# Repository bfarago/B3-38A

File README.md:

# B3-38A
B3-38A or V3-38A Russian Millivoltmeter

REVERSE ENGINEERING
-------------------
This repository contains all the collected informations regarding the old russian millivoltmeter instrument. The goal to collect datasheets, schematics, etc.

[BOM](rv_doc/bom.md), [Service Manual](rv_doc/B3-38A.pdf)

Technical characteristics
-------------------------
Millivoltmeter V3-38A (V3 38A, V338A, b3-38a, b338a, b3 38a)

Designed to measure the rms AC voltage sine wave of 0.1 mV to 300 V in the frequency range from 20 Hz to 5 MHz.
The span value of 1 mV, 3mV, 10mV, 30mV, 100mV, 300mV, 1V, 3V, 10V, 30V, 100V and 300V
The basic error of ± 2,5%

Millivoltmeter V3-38A is designed to measure the rms AC voltage sine wave of 0.1 mV to 300 V in the frequency range from 20 Hz to 5 MHz.
The operating conditions of use of the instrument Millivoltmeter V3-38A: ambient temperature from 10 ° to 35 ° C;
relative humidity. air 80% at 25 ° C, atmospheric pressure from 86 to 106 kPa (650 to 800 mm Hg. st.) mains (220 ± 22), frequency (50 ± 0,5) Hz .
Technical Data is a
Measurement range of the instrument voltages from 300V to 100mkV overlapping ranges with upper limits of 1 mV, 3mV, 10mV, 30mV, 100mV, 300mV, 1V, 3V, 10V, 30V, 100V and 300V. Instrument measures the voltage in the frequency range from 20 Hz to 5 MHz .
The range of frequencies of the device Millivoltmeter V3-38A has a working range of frequencies:
I from 45 Hz to 1 MHz (on);
II from 20 to 45 Hz (except);
III St.. 1 to 3 MHz (on);
IV St.. 3 to 5 MHz (inclusive).
Frequency of calibration of 1 kHz. Primary instrument error, expressed as a percentage of the upper limit established by sub-band measurements, no more than ± 2,5%.
Instrument error Millivoltmeter V3-38A in the working frequency regions, expressed as a percentage of the upper limit of the established sub-band, and the change of readings within the operating frequency ranges with respect to the frequency of calibration readings in percent, do not exceed the values shown in Table. 1.

Table 1: The limits of permissible errors (beyond the assumed changes of reading),%

| Subranges | I.: 45Hz- 1 MHz | II.: 20 - 45 Hz | III.:  1 - 3 MHz | IV.: 3 - 5 MHz |
| --- | --- | --- | --- | --- |
| 1 mV-300mV | ± 2,5 % | ± 4,0 (± 4,0) % | ± 4,0 (± 4,0) % | ± 6,0 (± 6,0) % |
| 1V-300V | ± 2,5 % | ± 4,0 (± 4,0) % | ± 6,0 (± 6,0) % | ± 6,0 (± 6,0) % |

Change readings, caused by changes in temperature. Ambient air from the normal to any temperature within the operating temperature range does not exceed the basic error for every 10 ° C change in temperature.
Change readings Millivoltmeter V3-38A, expressed as a percentage of the upper limit established by sub-band, rejecting the shape of the measured voltage from the sinusoidal (THD less than 20%) is less than half the value of the harmonic content in percent.
The deviation of the index from scratch, due to the intrinsic noise does not exceed 5% of the upper limit established by sub-band measurements with closed-circuit input.
The device retains its specifications within the rules, if its input DC voltage is not more than 250-V
Response time the device is less than 4 seconds.
Millivoltmeter V3-38A save tons of basic error handling five times after exposure to stress, but not more than 600 V.
Active impedance device, measured at a frequency of 45 Hz, less than 5 megohms at subbands upper limits 1-300mV and at least 4 Mohms subbands upper limits in 1-300
Input capacitance unit is not more than 25 pF subbands upper limits of 1-300 mV and not more than 15 pF subbands upper limits of 1-300 W.
The capacity of each of the connecting cable is not more than 80 pF. Warm-up time 15 min. Millivoltmeter V3-38A retains its specifications when powered from the mains AC voltage (220 ± 22) V (50 ± 0,5) Hz.
The power consumed by the network at a nominal voltage not exceeding 6 VA. Device allows continuous operation in the working conditions for 8 hours

Unit weight Millivoltmeter V3-38A or less than 3.2 kg.

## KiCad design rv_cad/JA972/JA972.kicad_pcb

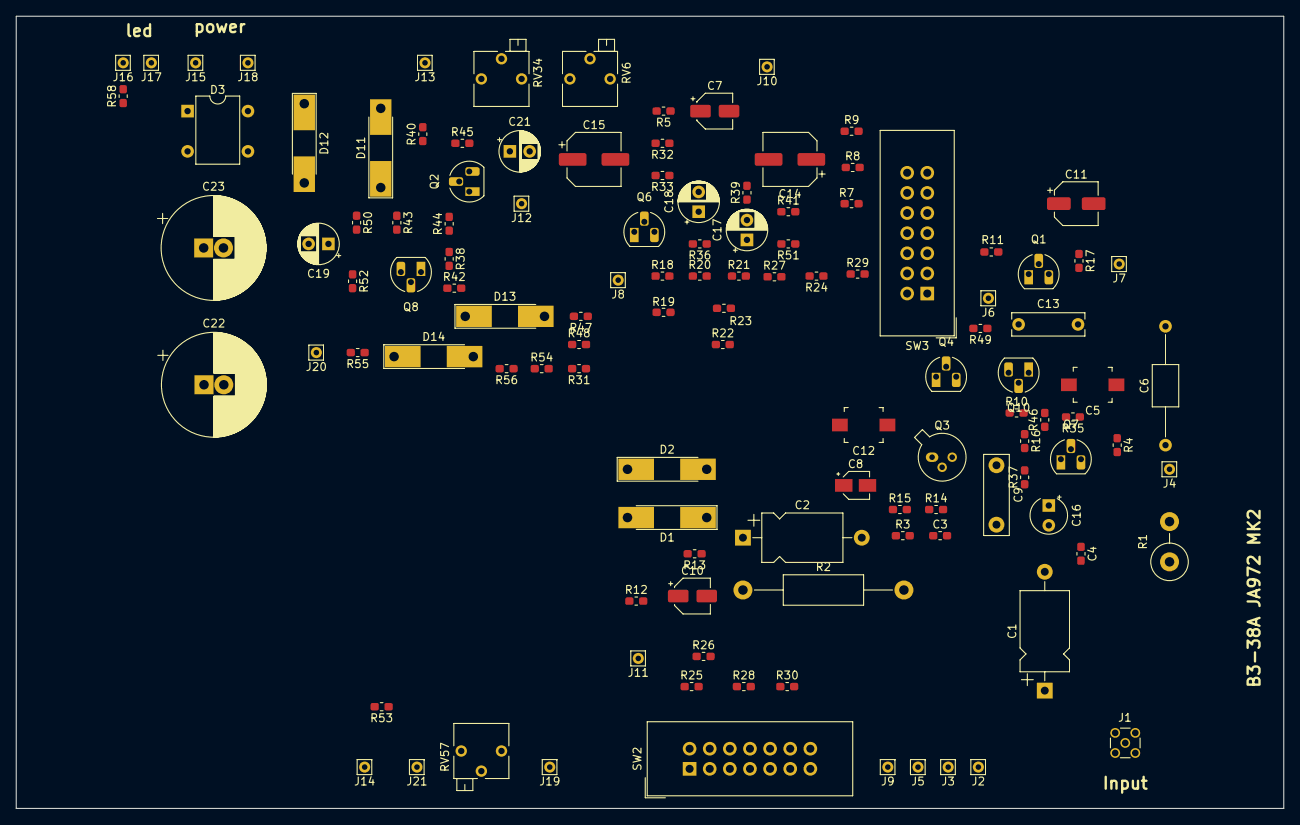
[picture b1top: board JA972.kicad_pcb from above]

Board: 2 copper layers, 160.0 x 100.0 mm, 118 parts (0 on the bottom side), 61 nets, no tracks yet.

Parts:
C1: 1600 500V 5%; CP_Axial_L10.0mm_D6.0mm_P15.00mm_Horizontal
C2: 2700 500V 5%; CP_Axial_L10.0mm_D6.0mm_P15.00mm_Horizontal
C3: 150 10%; C_0603_1608Metric_Pad1.05x0.95mm_HandSolder
C4: 2p2; C_0603_1608Metric_Pad1.05x0.95mm_HandSolder
C5: 2/7; C_Trimmer_Murata_TZB4-B
C6: 0,047uF/400V/10%; C_Axial_L5.1mm_D3.1mm_P15.00mm_Horizontal
C7: 200u/25V; CP_Elec_4x5.4
C8: 1u/6v3; CP_Elec_3x5.3
C9: 15+-10%/ M47; C_Rect_L10.0mm_W3.0mm_P7.50mm_FKS3_FKP3
C10: 22u/20v; CP_Elec_4x5.8
C11: 200u/25v; CP_Elec_5x5.8
C12: CTRIM; C_Trimmer_Murata_TZB4-B
C13: 15+-10%/ M47; C_Rect_L9.0mm_W2.7mm_P7.50mm_MKT
C14: 200u/25v; CP_Elec_6.3x5.4_Nichicon
C15: 100u/6v3; CP_Elec_6.3x5.4_Nichicon
C16: x; CP_Radial_Tantal_D4.5mm_P2.50mm
C17, C18, C19: x; CP_Radial_D5.0mm_P2.50mm
C21: 200u/25v; CP_Radial_D5.0mm_P2.50mm
C22: 100u/50v; CP_Radial_D13.0mm_P2.50mm
C23: 50u/100v; CP_Radial_D13.0mm_P2.50mm
D1, D2, D13, D14: KD522B; D_MELF-RM10_Universal_Handsoldering
D3: D_Bridge_+-AA; Diode_Bridge_DIP-4_W7.62mm_P5.08mm
D11, D12: 12V; D_MELF-RM10_Universal_Handsoldering
J1: Conn_Coaxial; MMCX_Molex_73415-1471_Vertical
J2: PGM_SWITCH1; Pin_D0.7mm_L6.5mm_W1.8mm_FlatFork
J3, J5: PGM_SWITCH2; Pin_D0.7mm_L6.5mm_W1.8mm_FlatFork
J4: PGM_SWITCH3; Pin_D0.7mm_L6.5mm_W1.8mm_FlatFork
J6: E1; Pin_D0.7mm_L6.5mm_W1.8mm_FlatFork
J7, J8: P7; Pin_D0.7mm_L6.5mm_W1.8mm_FlatFork
J9, J10: P10; Pin_D0.7mm_L6.5mm_W1.8mm_FlatFork
J11: P11; Pin_D0.7mm_L6.5mm_W1.8mm_FlatFork
J12: E2; Pin_D0.7mm_L6.5mm_W1.8mm_FlatFork
J13: E3; Pin_D0.7mm_L6.5mm_W1.8mm_FlatFork
J14: P6; Pin_D0.7mm_L6.5mm_W1.8mm_FlatFork
J15: P2; Pin_D0.7mm_L6.5mm_W1.8mm_FlatFork
J16: P4; Pin_D0.7mm_L6.5mm_W1.8mm_FlatFork
J17: P1; Pin_D0.7mm_L6.5mm_W1.8mm_FlatFork
J18: P3; Pin_D0.7mm_L6.5mm_W1.8mm_FlatFork
J19, J20, J21: P5; Pin_D0.7mm_L6.5mm_W1.8mm_FlatFork
Q1, Q2, Q4, Q6, Q7, Q8, Q10: 3107B; TO-92_HandSolder
Q3: kp103l; TO-18-3
R1: 7k5; R_Axial_DIN0414_L11.9mm_D4.5mm_P5.08mm_Vertical
R2: 5k11; R_Axial_DIN0411_L9.9mm_D3.6mm_P20.32mm_Horizontal
R3: 21,8; R_0603_1608Metric_Pad1.05x0.95mm_HandSolder
R4: 5M11; R_0603_1608Metric_Pad1.05x0.95mm_HandSolder
R5: 47k; R_0603_1608Metric_Pad1.05x0.95mm_HandSolder
R7, R44: 510; R_0603_1608Metric_Pad1.05x0.95mm_HandSolder
R8: 2M7; R_0603_1608Metric_Pad1.05x0.95mm_HandSolder
R9: 220k; R_0603_1608Metric_Pad1.05x0.95mm_HandSolder
R10, R35: 5k6; R_0603_1608Metric_Pad1.05x0.95mm_HandSolder
R11, R13: 3k; R_0603_1608Metric_Pad1.05x0.95mm_HandSolder
R12: 51; R_0603_1608Metric_Pad1.05x0.95mm_HandSolder
R14, R38, R39, R47, R50, R51: 1k; R_0603_1608Metric_Pad1.05x0.95mm_HandSolder
R15: 402; R_0603_1608Metric_Pad1.05x0.95mm_HandSolder
R16: 390; R_0603_1608Metric_Pad1.05x0.95mm_HandSolder
R17: 150; R_0603_1608Metric_Pad1.05x0.95mm_HandSolder
R18, R21, R24, R27: 56k; R_0603_1608Metric_Pad1.05x0.95mm_HandSolder
R19, R22, R25, R28, R30: 357; R_0603_1608Metric_Pad1.05x0.95mm_HandSolder
R20, R23, R26, R29, R52: 240; R_0603_1608Metric_Pad1.05x0.95mm_HandSolder
R31: 165; R_0603_1608Metric_Pad1.05x0.95mm_HandSolder
R32: 22k; R_0603_1608Metric_Pad1.05x0.95mm_HandSolder
R33, R37: 110; R_0603_1608Metric_Pad1.05x0.95mm_HandSolder
R36: 10; R_0603_1608Metric_Pad1.05x0.95mm_HandSolder
R40: 33k; R_0603_1608Metric_Pad1.05x0.95mm_HandSolder
R41: 100; R_0603_1608Metric_Pad1.05x0.95mm_HandSolder
R42, R45: 2k2; R_0603_1608Metric_Pad1.05x0.95mm_HandSolder
R43: 15; R_0603_1608Metric_Pad1.05x0.95mm_HandSolder
R46: 680; R_0603_1608Metric_Pad1.05x0.95mm_HandSolder
R48: 55,6; R_0603_1608Metric_Pad1.05x0.95mm_HandSolder
R49: 91; R_0603_1608Metric_Pad1.05x0.95mm_HandSolder
R53, R54: 1M; R_0603_1608Metric_Pad1.05x0.95mm_HandSolder
R55, R56: 2,49k; R_0603_1608Metric_Pad1.05x0.95mm_HandSolder
R58: 6k8; R_0603_1608Metric_Pad1.05x0.95mm_HandSolder
RV6: 33k; Potentiometer_Bourns_3266P_Horizontal
RV34: 220k; Potentiometer_Bourns_3266P_Horizontal
RV57: 1k5; Potentiometer_Bourns_3266P_Horizontal
SW2, SW3: SW_Rotary12; IDC-Header_2x07_P2.54mm_Vertical

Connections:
/P7: C11.2, C13.2, J7.1, J8.1, R17.1, R18.1, R19.1
/P8: C5.1, C6.1, J3.1, J5.1, R4.1
/PE2: J12.1, Q2.1, Q10.3, R16.2, R35.2, R37.2, R42.2, R46.1
GNDA: C1.1, C2.1, C7.2, C9.2, C10.2, C12.2, C15.1, C16.2, C19.2, C22.1, C23.1, D3.1, D12.2, J1.2, J11.1, J15.1, R2.1, R3.1, R13.1, R15.1, R20.2, R23.2, R26.2, R29.2, R31.2, R36.1, R38.1, R44.1, R45.1, R48.1, RV6.3, SW3.7, SW3.8, SW3.9, SW3.10, SW3.11, SW3.12
unnamed: C1.2, R1.1
unnamed: C2.2, C3.2, J4.1, R1.2, R2.2
unnamed: C3.1, R3.2
unnamed: C4.1, C5.2
unnamed: C4.2, J1.1, J2.1, R4.2
unnamed: C6.2, R7.2
unnamed: C7.1, Q1.1, R5.1, R10.2, R11.2, R16.1
unnamed: C8.1, D1.2, D2.1, R8.1, R9.2
unnamed: C9.1, Q3.3, Q4.2, R10.1
unnamed: C10.1, R12.1, R13.2
unnamed: C11.1, J6.1, Q1.3, R14.2
unnamed: C8.2, C12.1, Q3.1, R14.1, R15.2
unnamed: C13.1, R17.2, SW3.1, SW3.2
unnamed: C14.1, J10.1
unnamed: C14.2, R32.1, R33.1
unnamed: C15.2, R32.2, RV34.2, RV34.3
unnamed: C16.1, Q7.1, R37.1
unnamed: C17.1, C18.1, R41.2, R51.2
unnamed: C17.2, Q6.3, R36.2, R39.1, R41.1
unnamed: C18.2, R39.2
unnamed: C19.1, Q8.3, R43.2
unnamed: C21.1, D13.1, D14.2
unnamed: C21.2, J13.1, Q2.3, R45.2
unnamed: C22.2, R49.2, R50.2, R52.1
unnamed: C23.2, D3.2, R52.2, R58.1
unnamed: D1.1, D2.2, Q3.2, R7.1, R8.2
unnamed: D3.3, J17.1
unnamed: D3.4, J18.1
unnamed: D11.1, Q10.2, R50.1
unnamed: D11.2, D12.1
unnamed: D13.2, R47.2, R54.1, R56.1
unnamed: D14.1, R53.1, R55.1
unnamed: J9.1, SW2.13
unnamed: J14.1, R53.2
unnamed: J16.1, R58.2
unnamed: J19.1, R54.2
unnamed: J20.1, R55.2
unnamed: J21.1, RV57.1, RV57.2
unnamed: Q1.2, Q4.1, R11.1
unnamed: Q2.2, Q8.1, R42.1
unnamed: Q4.3, R12.2
unnamed: Q6.1, Q7.2, R35.1
unnamed: Q6.2, R33.2
unnamed: Q7.3, Q8.2, R38.2
unnamed: Q10.1, R46.2, R49.1
unnamed: R5.2, RV6.1
unnamed: R9.1, RV6.2
unnamed: R18.2, R19.2, R20.1, R21.1, R22.1, SW3.3, SW3.4
unnamed: R21.2, R22.2, R23.1, R24.1, R25.1, SW3.5, SW3.6
unnamed: R24.2, R25.2, R26.1, R27.1, R28.1, SW2.7, SW2.8
unnamed: R27.2, R28.2, R29.1, R30.1, SW2.9, SW2.10, SW2.11
unnamed: R30.2, R31.1, SW2.12
unnamed: R40.1, R43.1, R44.2
unnamed: R40.2, RV34.1
unnamed: R47.1, R48.2
unnamed: R56.2, RV57.3
unnamed: SW2.1, SW2.2, SW2.3, SW2.4, SW2.5, SW2.6, SW3.13

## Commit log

2019-06-10 initial
2019-06-11 Original service manual
